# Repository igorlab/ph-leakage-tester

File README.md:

# ph-leakage-tester

Open hardware: a pH electrode simulator and leakage tester for in-circuit estimation of the
input current of a pH amplifier. A battery cell sets a known "electrode" voltage E, a known
series resistor R replaces the electrode, and the amplifier output gives the input current
from the drop across R. Currents of 18 pA to 1.7 nA applied through a known resistor were
recovered; below about 10 pA the reading is only an indication.

Description, build instructions, validation and limitations: see the HardwareX article
(in preparation).

## At a glance

*The tester on a 1 cm grid, with its BNC cable.*

*Principle: the simulator voltage E is measured before the series resistor R. With R shorted the input equals E and two points give the amplifier's transfer line; with R in circuit the input is recovered from the output and the current is (Vin − E)/R.*

*Check against known currents: a 9.73 MΩ resistor connected and removed at E = 100, 30 and 10 mV; measured currents agree with the calculated ones within 0.3 %.*

*Input current of the isolated amplifier by the toggle method: the button is pressed and released in phases of 30–60 s, and slow drift cancels.*

## Contents

| Folder | What is in it |
|---|---|
| `hardware/` | KiCad schematic and BOM of the tester; `enclosure/` has the STL files for printing |
| `firmware/` | PlatformIO firmware for the ESP32-C3 (copy `src/wifi_secret.example.h` to `src/wifi_secret.h` and fill in your own Wi-Fi; that file is never committed). If the tester cannot join that network within 20 s, it starts its own access point “pH-Calibrator” with the default password `calib1234` (`AP_PASS` in `src/main.cpp`; change it if needed) |
| `tools/` | `calibrator_log.py` (CSV logger), `new_runs.py` (analysis of toggle and noise runs) |
| `analysis/` | `paper_numbers.py` recomputes every number in the paper from `data/` |
| `data/` | Raw measurement logs (CSV, never edited) with their own README |
| `figures/`, `photos/` | Figures of the paper and their scripts; photos without EXIF |
| `ph_board/` | The isolated pH amplifier used as the device under test: KiCad files, Gerbers, BOM |
| `LICENSES/` | Full texts of the licences below |

## Licences

- Hardware (KiCad, enclosure): CERN-OHL-S-2.0
- Firmware and scripts: GPL-3.0-or-later
- Documentation, figures and data: CC BY-SA 4.0

## Citation

Zenodo DOI: to be added after the first release.

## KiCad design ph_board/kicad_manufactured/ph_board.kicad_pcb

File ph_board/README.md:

# pH electrode front end: LMC6042 + HCNR201 + TMA0505D

A galvanically isolated electrometer front end for a glass pH electrode, made for an
automated KH titrator on an ESP32. Two measured revisions are retained. Revision A is
the first manufactured board with a divider-derived reference. Revision B replaces the
divider with a REF3040 and is the primary design for publication. Both are without
trimmers.

## Revisions and file status

| Revision | Reference | Evidence | Status of design files |
|---|---|---|---|
| A | R5 = 56 kΩ and R9 = 10 kΩ from the isolated +5 V rail | Protocols A, D, E and the original part of J | Archived BOM `fab/ph_board_bom_rev_a.csv`; the PCB/Gerbers are the common base |
| B | REF3040AIDBZR (U6), 47 kΩ / R9 = 10 kΩ divider | Board-B supply sweep after the 2026-10-24 rework | Primary publication revision; common PCB plus the documented R5/RA2 assembly rework and `fab/ph_board_bom.csv` |

Do not use measurements made on revision A as if they had been repeated on revision B.
The reference is outside the high-impedance input node and does not set the signal gain,
so the earlier gain, leakage and linearity results remain relevant to the unchanged
signal path, but revision B still requires its own post-rework control line, leakage and
linearity check. The measured supply sensitivity changed from 0.87 ± 0.02 pH/V of USB
on revision A to 0.002 ± 0.002 pH/V on revision B.

## Origin

The circuit is a revision of the pH interface that Franck ("Bubule") shared on the French
reef-keeping forum [cap-recifal.com](https://www.cap-recifal.com/forums/topic/668-ph-m%C3%A8tre-diy/) in 2011. With the original component values
the input stage, the second stage and the optocoupler failed when the electrode was
disconnected. The values were changed to stop this and to fit the output to the 0–3 V ADC
input of an ESP32, and the board was laid out anew. Thanks to Franck for sharing it.

The original schematic, *Interface pH pour Arduino isolé* (KiCad, 20 Sep 2011), is
[here](https://www.cap-recifal.com/sites/default/files/files/511/bubule_20111119195948.pdf). The topology is the same; what changed:

| Function | Original (2011) | This board |
|---|---|---|
| Input stage gain | 1 + 255k / (40k + 10k trimmer) | 1 + R3/R8 = 1 + 200k/39k = 6.13, fixed |
| Offset reference | 30k + 10k trimmer + 10k from 5 V (1–2 V) | Revision A: R5 56k / R9 10k from 5 V; revision B: REF3040 followed by 47k / R9 10k |
| Trimmers | two (full scale, pH 7) | none: RA1, RA2 are wire links |
| HCNR201 LED resistor | 255 Ω | R2 470 Ω |
| Servo loop capacitor | 10 pF | C5 56 nF |
| Output stage capacitor | 10 pF | C1 1 µF |
| Supply decoupling | 2.2 µF | 20 µF electrolytic + 1 µF ceramic |
| Isolated converter | DCV010505D | TMA 0505D |
| Input pin | on the board | in the air, straight to the BNC centre |
| Output | 0–5 V for pH 0–14 | 0.5–2.45 V for pH 4–9.4 (ESP32 ADC) |

## Contents

- [`kicad_manufactured/`](kicad_manufactured/): KiCad 10 project.
  - `ph_board.kicad_sch` is the schematic, `ph_board.kicad_pcb` the board.
  - `ph-board.kicad_sym` holds the symbols, `ph_single-easyedapro.pretty` the footprints.
  - `ph_board.kicad_dru` is the isolation rule: copper of the station side keeps 1.8 mm
    from the electrode side.
- [`fab/ph_board_gerbers.zip`](fab/ph_board_gerbers.zip): Gerbers and drill files, exactly the
  package that was ordered on 2026-10-02 (file names `ph_final-*`).
- [`fab/ph_board_bom.csv`](fab/ph_board_bom.csv): parts list.
- [`fab/ph_board_bom_rev_a.csv`](fab/ph_board_bom_rev_a.csv): archived divider-revision
  parts list. The unmodified KiCad schematic shows this base circuit.
- [`docs/ph_board_schematic.pdf`](docs/ph_board_schematic.pdf): the schematic for printing.

## How the files were checked

- The board was laid out first; the schematic was drawn after it, from its connections.
- `kicad_manufactured/ph_board.kicad_pcb` is the file the boards were ordered from (2026-10-02): KiCad
  regenerates the ordered copper, mask, paste and outline Gerbers from it without a
  single difference.
- DRC reports 0 unconnected pads. Schematic parity reports 132 mismatches (footprint
  names, values, net names): the schematic was drawn after the layout and has not been
  re-synchronised with this file. The input has no copper (see below).
- The Gerbers and drill files in `fab/` are the ones that were ordered (2026-10-02), so
  copper, mask and drill are those of the boards that were made. A release rebuilt on
  2026-10-20 differs in the silkscreen (labels moved, «igorlab 2026» added); by the board
  journal nothing else was changed.

## Building it

- **The input has no copper.** Bend U1 pin 5 up so that it touches nothing, and wire it in
  the air straight to the BNC centre. Solder only the shield of the BNC to the board.
- **RA1 and RA2 are not trimmers.** Bend a bare 0.5–0.6 mm wire into a staple, push it
  through holes 1 and 3, and solder it to hole 2 as well. This applies to revision A;
  revision B uses RA2 for its 47 kΩ divider as described below.
- **Two grounds.** GND is the electrode side, com the station side. U3 (HCNR201) and U7
  (TMA0505D) are the isolation barrier. Measure TP2–TP7 against TP1 and TP9 against TP8.
- **Cable to the calibrator.** P2 is 1 VCC, 2 com, 3 S. The calibrator's JST has +5 V in
  the middle, so the cable between them is crossed: wire it by function and check it before
  you power the board.
- **Wash the flux off** around U1 and the BNC: those nodes carry picoamps.

### Revision B: REF3040 assembly rework

Revision B uses the same PCB and Gerbers as revision A. Assemble the common board as
listed in `fab/ph_board_bom.csv`, with these changes:

1. Do not fit R5 (56 kΩ).
2. Place U6, REF3040AIDBZR (SOT-23-3), on the two R5 pads: pin 1 (IN) to the upper
   +5 V pad and pin 2 (OUT) to the lower pad leading to RA2 hole 1. Keep pin 3 (GND)
   clear of the RA2-hole-1 copper and wire it with insulated wire to GND at the lower
   pad of R8.
3. At RA2, fit 47 kΩ between holes 1 and 2 and a wire link between holes 2 and 3.
   R9 remains 10 kΩ and forms the lower arm to GND.
4. Inspect for shorts before power-up. Without power, RA2 hole 1 to TP1 should be about
   57 kΩ and U6 pin 3 to TP1 about 0 Ω.
5. Power the board with a current-limited 5 V supply and verify approximately 4.096 V
   at U6 OUT and approximately 0.72 V nominal at Vref/TP3. The measured prototype gave
   4.09 V and 0.688 V respectively.

The schematic image below shows the common revision-A PCB base. For revision B, replace
R5 with U6 and the 47 kΩ/R9 network exactly as specified above. This documented rework is
the configuration that was physically measured; an untested integrated PCB respin is not
presented as validated hardware.

## Parts

| Ref | Value | Notes |
|---|---|---|
| U1, U2, U4 | LMC6042AIM, SOIC-8 | From an authorised distributor |
| U3 | HCNR201-500E | Analog optocoupler |
| U7 | TMA 0505D | Isolated 5 V to ±5 V, 1 W. Check the pin numbers against your part's datasheet |
| U5 | BNC socket, PCB mount | Centre wired in the air to U1 pin 5 |
| P2 | JST XH, 3 pins | 1 VCC (+5 V), 2 com, 3 S |
| R1, R4 | 100k 0805 1 % | |
| R2 | 470 0805 1 % | HCNR201 LED current |
| R3 | 200k 0805 1 % | First-stage gain 1 + R3/R8 = 6.13 |
| R5 | not fitted in revision B | 56k 0805 1 % only in archived revision A |
| R10 | 47k 0805 1 % | Revision B: RA2 holes 1–2, upper arm from REF3040 OUT to Vref |
| R6, R7, R9 | 10k 0805 1 % | |
| R8 | 39k 0805 1 % | |
| C1, C6–C10 | 1 µF 0805 ceramic | As fitted; 100 nF works too. C1 ceramic only |
| C5 | 56 nF 0805 ceramic | Ceramic only, not 1 µF |
| C2–C4 | 20 µF electrolytic | Any 4.7–47 µF, 10 V or more. C3: + goes to GND |
| RA1 | wire link | See above |
| RA2 | 47k plus wire link | Revision B: 47k on holes 1–2, link on holes 2–3 |
| U6 | REF3040AIDBZR, SOT-23-3 | Revision B; mounted on R5 pads as described above |

Part numbers for the resistors are in [`fab/ph_board_bom.csv`](fab/ph_board_bom.csv).

## Measured results

| | |
|---|---|
| Slope | −6.27 V/V (−6.13 by design) |
| S at 0 mV | 1.692 V |
| Input current, revision A | below 1 pA with the calibrator and a fresh calibration line; the earlier multimeter-bound result was below 8 pA |
| Supply sensitivity, revision A | 0.87 ± 0.02 pH/V of USB |
| Supply sensitivity, revision B | 0.002 ± 0.002 pH/V of USB |

The board was tested with the calibrator from
[github.com/igorlab/ph-simulator](https://github.com/igorlab/ph-simulator).

## Licence

Hardware: CERN-OHL-S v2.

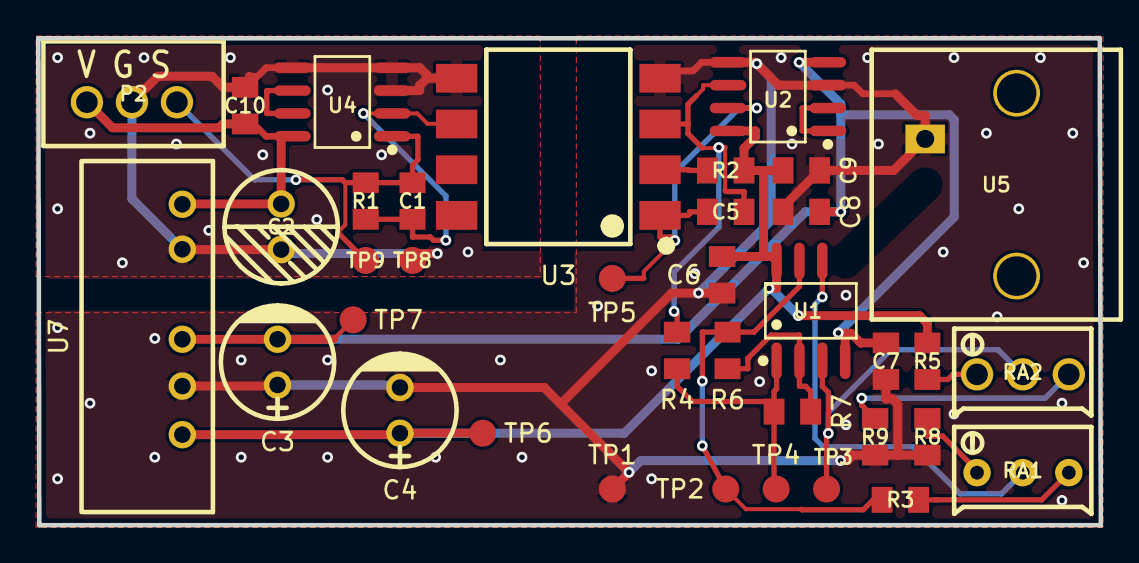
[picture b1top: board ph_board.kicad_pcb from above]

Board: 2 copper layers, 59.0 x 27.1 mm, 37 parts (0 on the bottom side), 21 nets.

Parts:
C1, C5, C6, C7, C8, C9, C10: 100nF; 0805
C2: 10uF; CAP-GT-6.3*7
C3, C4: 10uF; CAP-D6.3XF2.5
P2: XH-3A
R1, R4: 100k; 0805
R2: 470; 0805
R3: 220k; 0805
R5: 82k; 0805
R6, R7, R9: 10k; 0805
R8: 39k; 0805
RA1, RA2: 10k; RES-ADJ_3296W
TP1: GND; Test-Point-0.5mm
TP2: V1; Test-Point-0.5mm
TP3: Vref; Test-Point-0.5mm
TP4: V2; Test-Point-0.5mm
TP5: LED; Test-Point-0.5mm
TP6: +5V; Test-Point-0.5mm
TP7: -5V; Test-Point-0.5mm
TP8: com; Test-Point-0.5mm
TP9: S; Test-Point-0.5mm
U1, U2, U4: LMC6042; SOIC-8_L4.9-W3.8-P1.27-LS6.0-BL
U3: HCNR201; SMD-8_9.0MM
U5: BNC
U7: TMA0505D; TMA0505D_IL

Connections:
$2N1: R6.2, R7.1, U1.2
$2N2: RA1.2, U1.6
$2N3: R3.1, RA1.3
$2N4: R8.2, RA1.1
$2N5: R3.2, R6.1, TP2.1, U1.7
$2N6: R4.1, R7.2, TP4.1, U1.1
$2N7: RA2.2, TP3.1, U1.3
$2N9: C5.2, R4.2, U2.6, U3.3
$2N10: C5.1, TP5.1, U2.7, U3.1
$2N11: C1.1, R1.1, U3.6, U4.2
$2N12: C1.2, P2.3, R1.2, TP9.1, U4.1
$2N17: R2.2, U3.2
$2N21: R9.2, RA2.3
$2N24: R5.1, RA2.1
$2N52: U4.6, U4.7
$2N66: U2.1, U2.2
+5V: C4.1, C6.2, C9.2, R2.1, R5.2, TP6.1, U1.8, U2.8, U7.6
-5V: C3.2, C7.1, C8.1, TP7.1, U1.4, U2.4, U7.4
GND: C3.1, C4.2, C6.1, C7.2, C8.2, C9.1, R8.1, R9.1, TP1.1, U2.3, U2.5, U3.4, U5.GND, U7.5
VCC: C2.1, C10.1, P2.1, U4.8, U7.1
com: C2.2, C10.2, P2.2, TP8.1, U3.5, U4.3, U4.4, U4.5, U7.2
